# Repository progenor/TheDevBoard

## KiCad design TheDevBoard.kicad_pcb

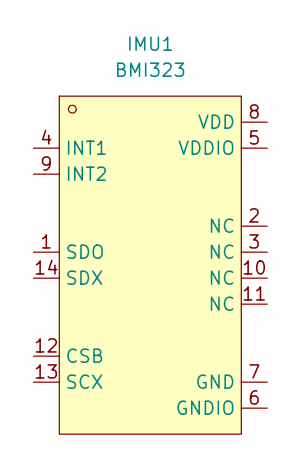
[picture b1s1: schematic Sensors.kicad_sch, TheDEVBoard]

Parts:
IMU1: BMI323; LGA-14_L3.0-W2.5-P0.50-TL_QMI8658A; MPN BMI323; LCSC Part C5368700

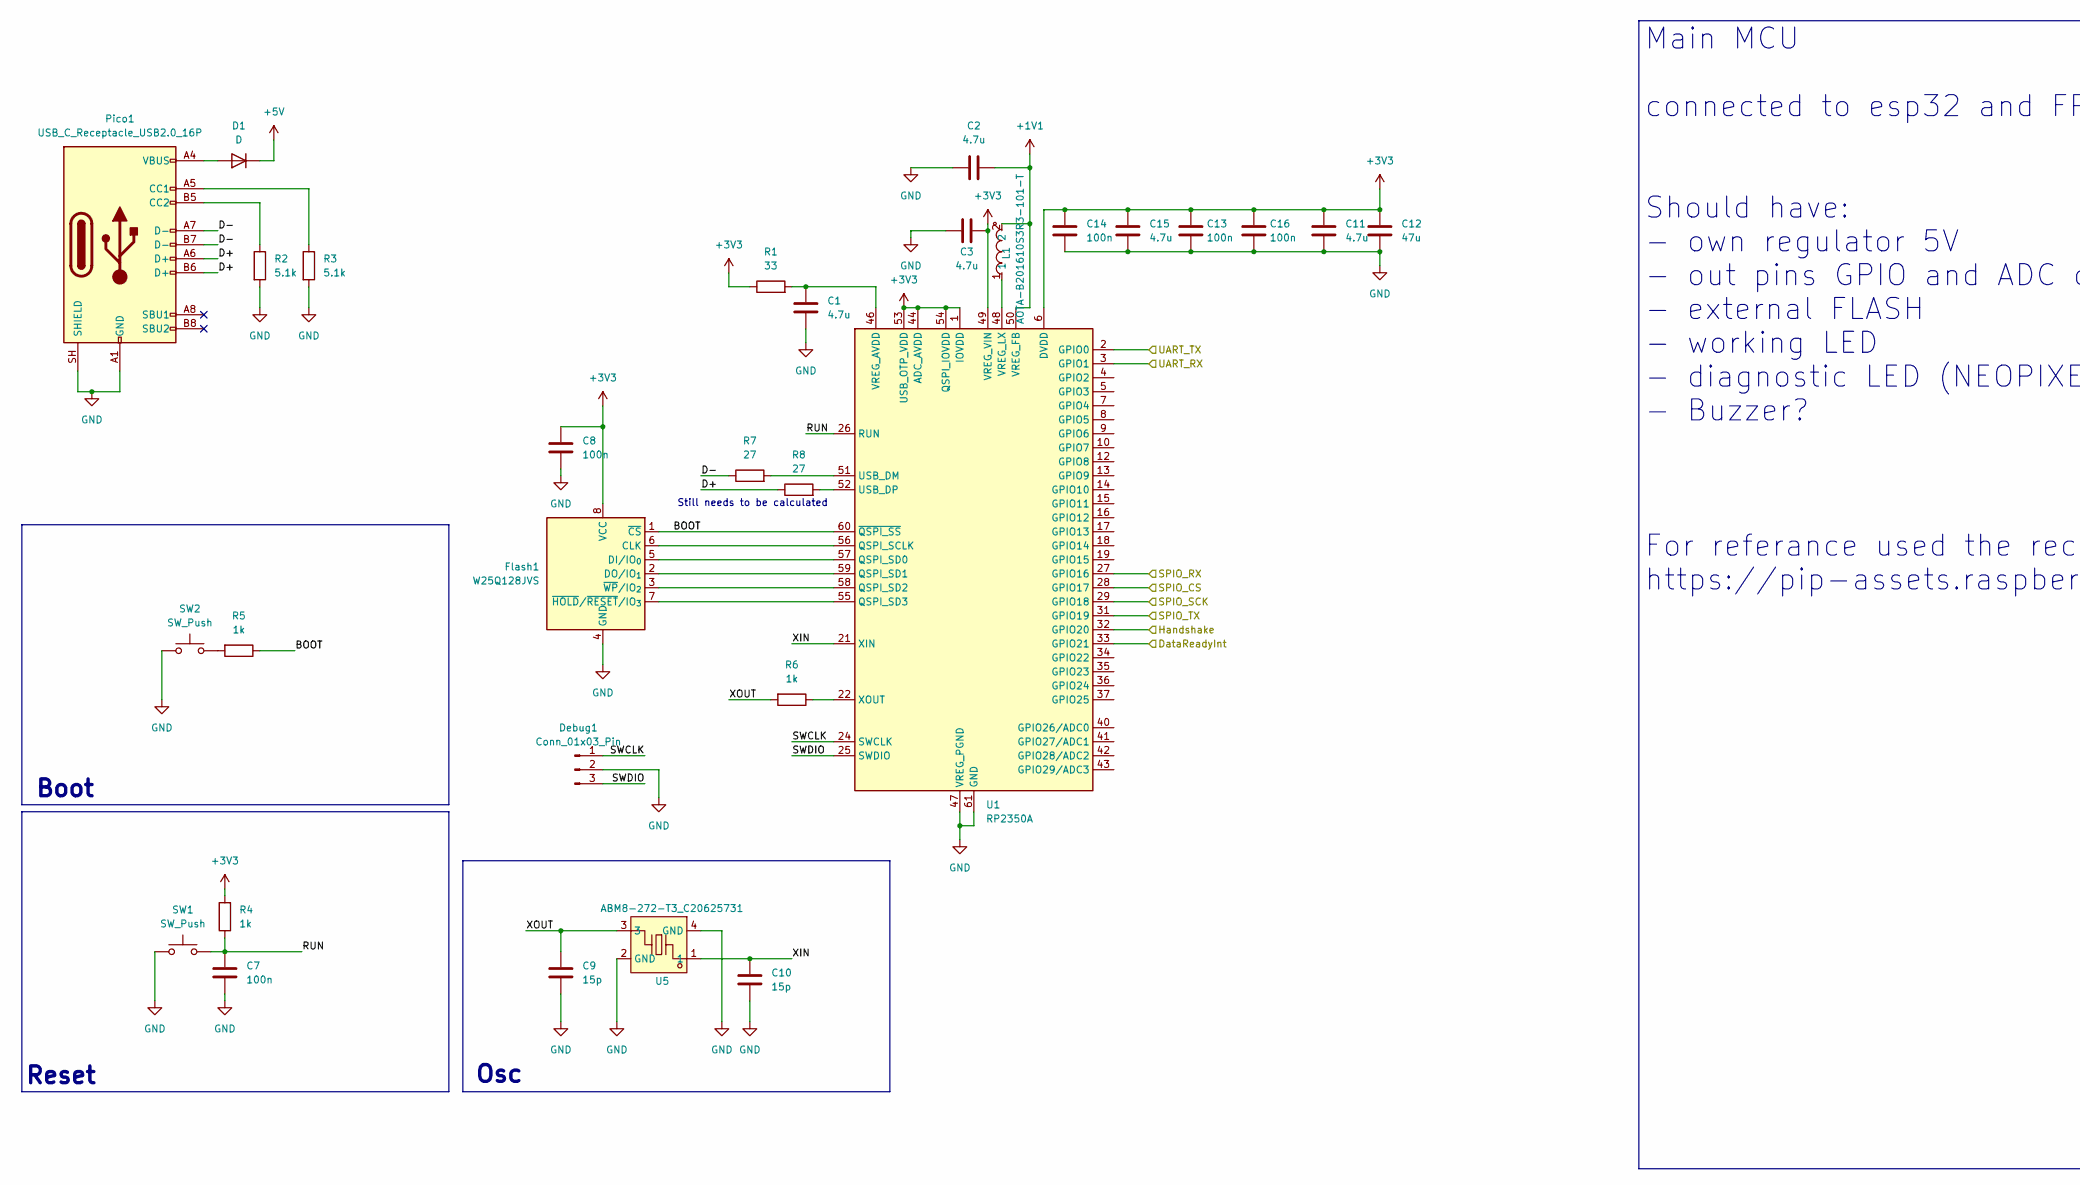
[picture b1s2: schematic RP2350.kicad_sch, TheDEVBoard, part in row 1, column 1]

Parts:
C1, C2, C3, C11, C15: 4.7u; C_0201_0603Metric_Pad0.64x0.40mm_HandSolder
C7, C8, C13, C14, C16: 100n; C_0805_2012Metric_Pad1.18x1.45mm_HandSolder
C9, C10: 15p; C_0805_2012Metric_Pad1.18x1.45mm_HandSolder
C12: 47u; C_0805_2012Metric_Pad1.18x1.45mm_HandSolder
D1: D; D_0805_2012Metric
Debug1: Conn_01x03_Pin; PinHeader_1x03_P2.54mm_Vertical
Flash1: W25Q128JVS; SOIC-8_5.3x5.3mm_P1.27mm
L1: AOTA-B201610S3R3-101-T; IND-SMD_L2.0-W1.6_AOTA-B201610S3R3-101-T; MPN AOTA-B201610S3R3-101-T; LCSC Part C42411119
Pico1: USB_C_Receptacle_USB2.0_16P; USB_C_Receptacle_XKB_U262-16XN-4BVC11
R1: 33; R_0201_0603Metric_Pad0.64x0.40mm_HandSolder
R2, R3: 5.1k; R_0805_2012Metric_Pad1.20x1.40mm_HandSolder
R4, R5, R6: 1k; R_0805_2012Metric_Pad1.20x1.40mm_HandSolder
R7, R8: 27; R_0805_2012Metric_Pad1.20x1.40mm_HandSolder
SW1, SW2: SW_Push; SW_SPST_EVQPE1
U1: RP2350A; QFN-60-1EP_7x7mm_P0.4mm_EP3.4x3.4mm
U5: ABM8-272-T3_C20625731; CRYSTAL-SMD_4P-L3.2-W2.5-BL; MPN ABM8-272-T3; LCSC Part C20625731

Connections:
+1V1: C2.2, L1.2, U1.50 (VREG_FB)
+3V3: C3.2, C8.1, C11.1, C12.1, C13.1, C14.1, C15.1, C16.1, Flash1.8 (VCC), R1.1, R4.2, U1.1 (IOVDD), U1.6 (DVDD), U1.11 (IOVDD), U1.20 (IOVDD), U1.23 (DVDD), U1.30 (IOVDD), U1.38 (IOVDD), U1.39 (DVDD), U1.44 (ADC_AVDD), U1.45 (IOVDD), U1.49 (VREG_VIN), U1.53 (USB_OTP_VDD), U1.54 (QSPI_IOVDD); also elsewhere on the board
+5V: D1.1 (K); also elsewhere on the board
/ESP32-S3-Mini-WIFI/DataReadyInt: U1.33 (GPIO21); also elsewhere on the board
/ESP32-S3-Mini-WIFI/FSPICLK: U1.29 (GPIO18); also elsewhere on the board
/ESP32-S3-Mini-WIFI/FSPICS0: U1.28 (GPIO17); also elsewhere on the board
/ESP32-S3-Mini-WIFI/FSPID: U1.31 (GPIO19); also elsewhere on the board
/ESP32-S3-Mini-WIFI/FSPIQ: U1.27 (GPIO16); also elsewhere on the board
/ESP32-S3-Mini-WIFI/Handshake: U1.32 (GPIO20); also elsewhere on the board
/ESP32-S3-Mini-WIFI/UART_RX_ESP: U1.2 (GPIO0); also elsewhere on the board
/ESP32-S3-Mini-WIFI/UART_TX_ESP: U1.3 (GPIO1); also elsewhere on the board
/RP2350/<NO NET>: Pico1.A7 (D-), Pico1.B7 (D-), R7.1
/RP2350/BOOT: Flash1.1 (~CS), R5.1, U1.60 (~QSPI_SS); also elsewhere on the board
/RP2350/D+: Pico1.A6 (D+), Pico1.B6 (D+), R8.1
/RP2350/RUN: C7.1, R4.1, SW1.2, U1.26 (RUN)
/RP2350/SWCLK: Debug1.1, U1.24 (SWCLK)
/RP2350/SWDIO: Debug1.3, U1.25 (SWDIO)
/RP2350/XIN: C10.1, U1.21 (XIN), U5.1
/RP2350/XOUT: C9.1, R6.2, U5.3
GND: C1.2, C2.1, C3.1, C7.2, C8.2, C9.2, C10.2, C11.2, C12.2, C13.2, C14.2, C15.2, C16.2, Debug1.2, Flash1.4 (GND), Pico1.A1 (GND), Pico1.A12 (GND), Pico1.B1 (GND), Pico1.B12 (GND), Pico1.SH (SHIELD), R2.2, R3.2, SW1.1, SW2.1, U1.47 (VREG_PGND), U1.61 (GND), U5.2 (GND), U5.4 (GND); also elsewhere on the board
unnamed: D1.2 (A), Pico1.A4 (VBUS), Pico1.A9 (VBUS), Pico1.B4 (VBUS), Pico1.B9 (VBUS)
unnamed: Flash1.6 (CLK), U1.56 (QSPI_SCLK)
unnamed: Flash1.5 (DI/IO_{0}), U1.57 (QSPI_SD0)
unnamed: Flash1.2 (DO/IO_{1}), U1.59 (QSPI_SD1)
unnamed: Flash1.7 (~HOLD/~RESET/IO_{3}), U1.55 (QSPI_SD3)
unnamed: Flash1.3 (~WP/IO_{2}), U1.58 (QSPI_SD2)
unnamed: Pico1.A5 (CC1), R3.1
unnamed: Pico1.B5 (CC2), R2.1
unnamed: R5.2, SW2.2
unnamed: R7.2, U1.51 (USB_DM)
unnamed: R8.2, U1.52 (USB_DP)
unnamed: C1.1, R1.2, U1.46 (VREG_AVDD)
unnamed: L1.1, U1.48 (VREG_LX)
unnamed: R6.1, U1.22 (XOUT)

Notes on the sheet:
Boot
Reset
Still needs to be calculated
Osc
Main MCU connected to esp32 and FPGA Should have: - own regulator 5V - out pins GPIO and ADC convertor - external FLASH - working LED - diagnostic LED (NEOPIXEL) - Buzzer? For referance used the recomended design by Raspbery itself https://pip-assets.raspberrypi.com/categories/1214-rp2350/documents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

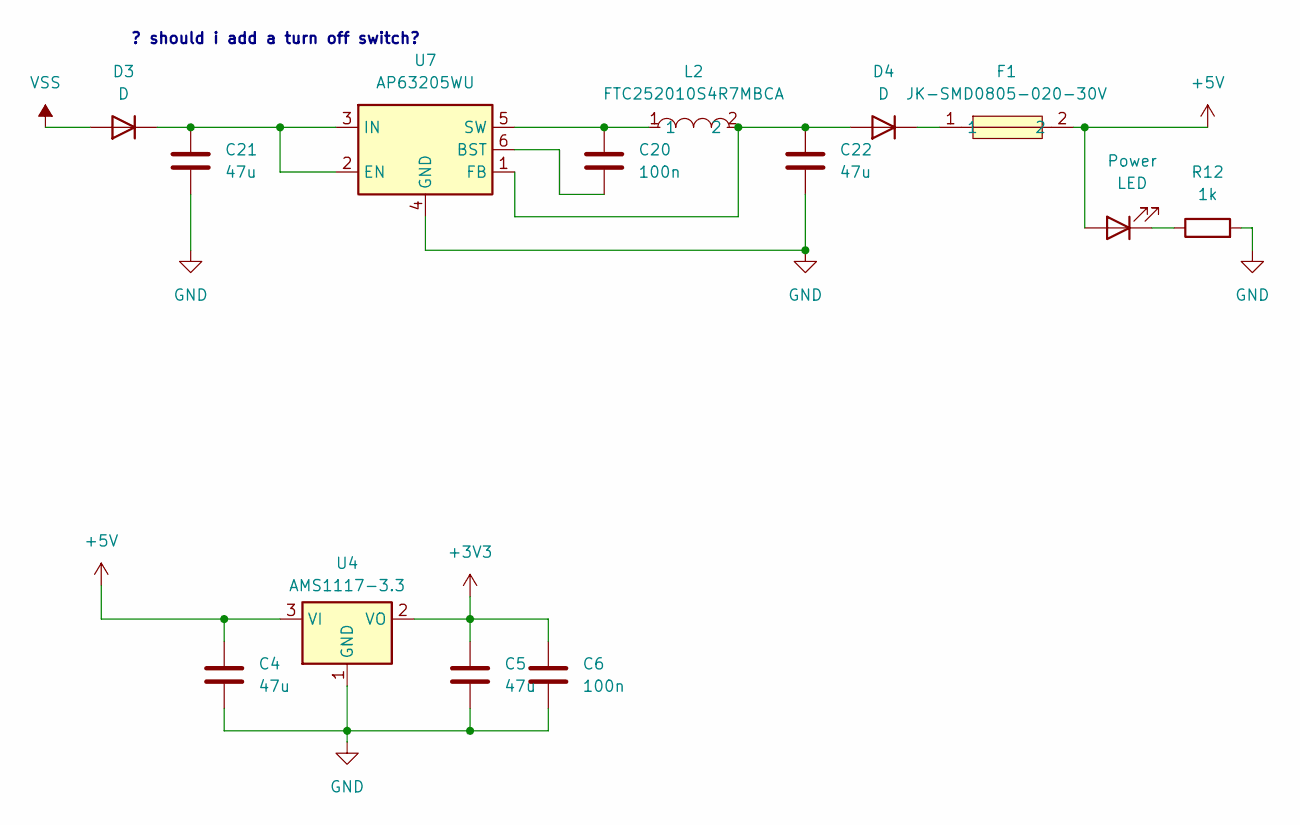
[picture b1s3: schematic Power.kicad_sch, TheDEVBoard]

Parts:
C4, C5, C21, C22: 47u; C_0805_2012Metric_Pad1.18x1.45mm_HandSolder
C6, C20: 100n; C_0805_2012Metric_Pad1.18x1.45mm_HandSolder
D3, D4: D; D_0805_2012Metric
F1: JK-SMD0805-020-30V; F0805; MPN JK-SMD0805-020-30V; LCSC Part C516070
L2: FTC252010S4R7MBCA; IND-SMD_L2.5-W2.0-VLS252012CX-150M; MPN FTC252010S4R7MBCA; LCSC Part C5832360
Power: LED; LED_0805_2012Metric
R12: 1k; R_0805_2012Metric
U4: AMS1117-3.3; SOT-223-3_TabPin2
U7: AP63205WU; TSOT-23-6_HandSoldering

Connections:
+3V3: C5.1, C6.1, U4.2 (VO); also elsewhere on the board
+5V: C4.1, F1.2, Power.2 (A), U4.3 (VI); also elsewhere on the board
GND: C4.2, C5.2, C6.2, C21.2, C22.2, R12.2, U4.1 (GND), U7.4 (GND); also elsewhere on the board
unnamed: C21.1, D3.1 (K), U7.2 (EN), U7.3 (IN)
unnamed: C22.1, D4.2 (A), L2.2, U7.1 (FB)
unnamed: D4.1 (K), F1.1
unnamed 42: Power.1 (K), R12.1; also elsewhere on the board
unnamed: C20.2, U7.6 (BST)
unnamed: C20.1, L2.1, U7.5 (SW)
VSS: D3.2 (A)

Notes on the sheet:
? should i add a turn off switch?

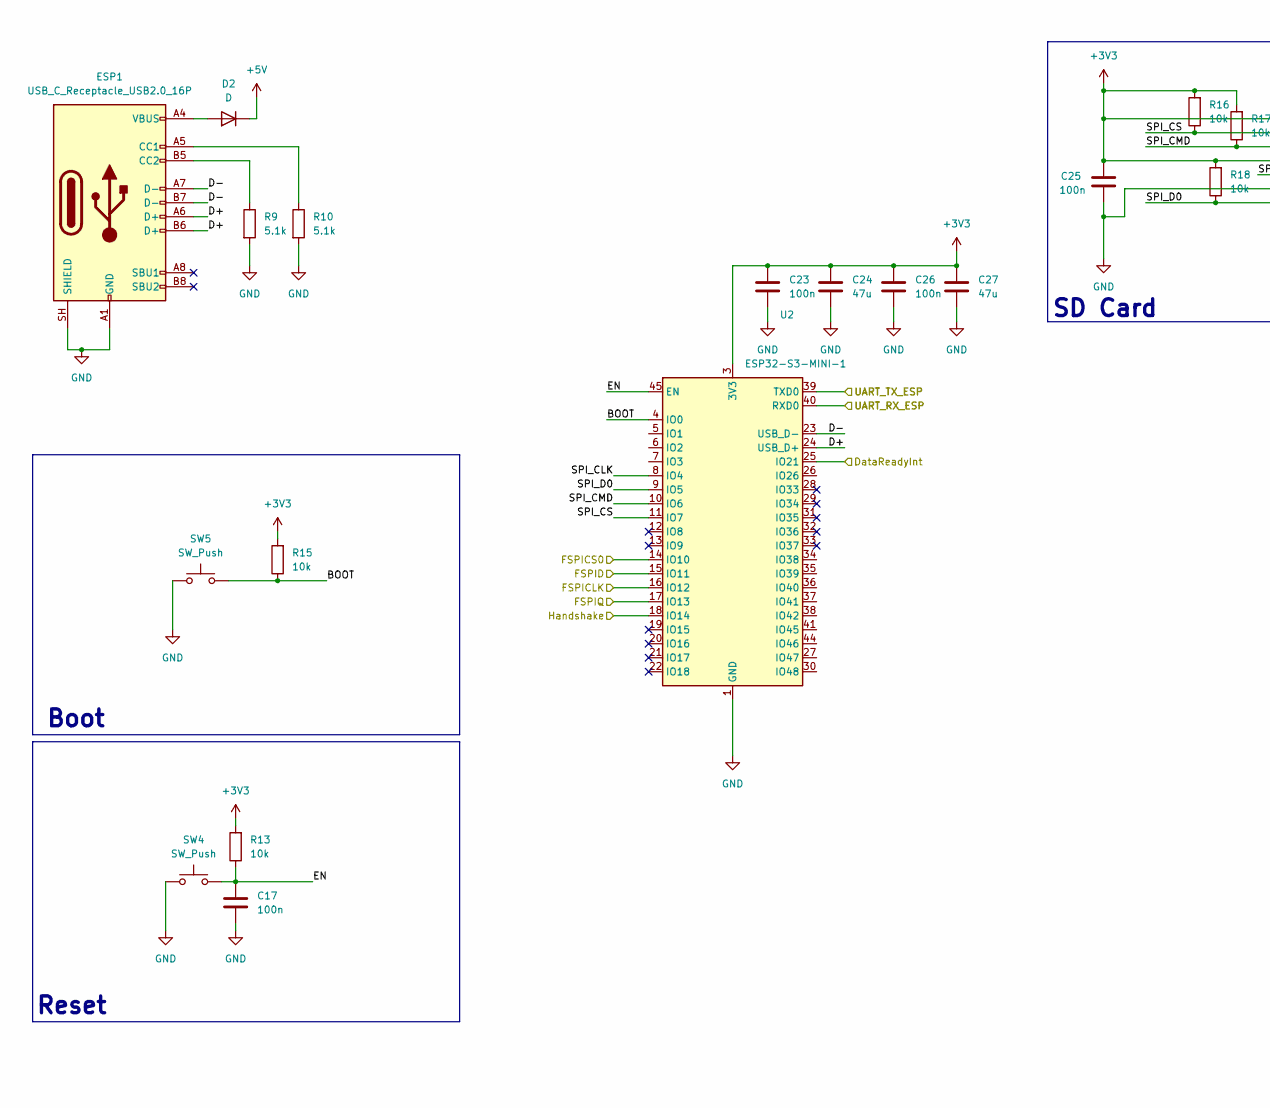
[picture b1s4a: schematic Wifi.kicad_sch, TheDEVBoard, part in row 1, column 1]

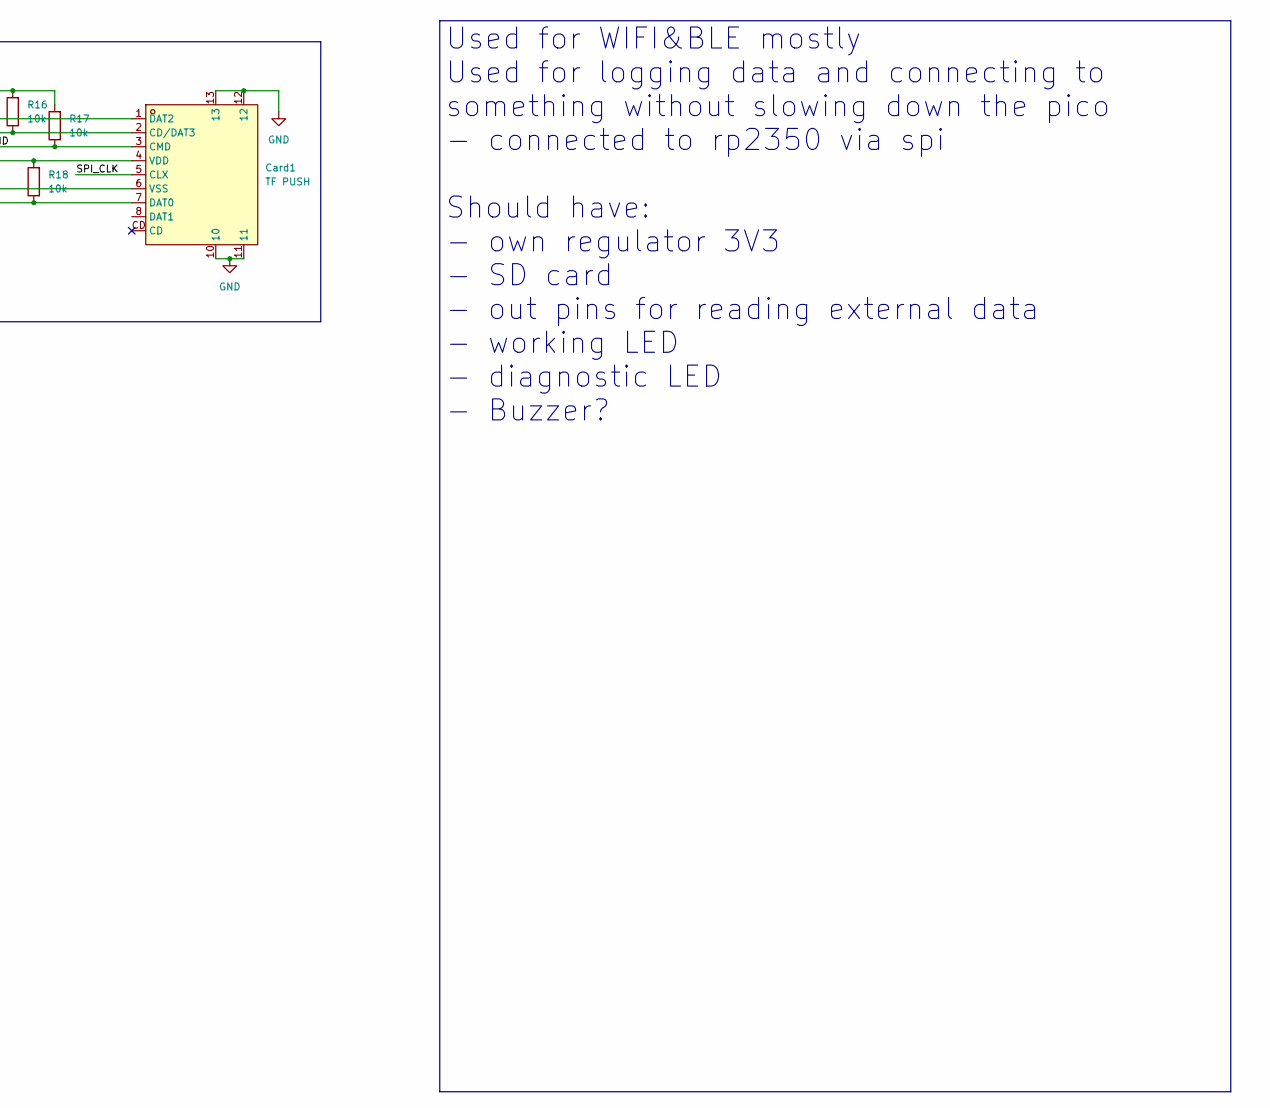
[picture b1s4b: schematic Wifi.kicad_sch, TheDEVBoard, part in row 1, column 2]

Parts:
C17, C23, C25, C26: 100n; C_0805_2012Metric_Pad1.18x1.45mm_HandSolder
C24, C27: 47u; C_0805_2012Metric_Pad1.18x1.45mm_HandSolder
Card1: TF PUSH; TF-SMD_TF-PUSH; MPN TF PUSH; LCSC Part C393941
D2: D; D_0805_2012Metric
ESP1: USB_C_Receptacle_USB2.0_16P; USB_C_Receptacle_XKB_U262-16XN-4BVC11
R9, R10: 5.1k; R_0805_2012Metric_Pad1.20x1.40mm_HandSolder
R13, R15, R16, R17, R18: 10k; R_0805_2012Metric_Pad1.20x1.40mm_HandSolder
SW4, SW5: SW_Push; SW_SPST_EVQPE1
U2: ESP32-S3-MINI-1; ESP32-S2-MINI-1

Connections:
+3V3: C23.1, C24.1, C25.1, C26.1, C27.1, Card1.1 (DAT2), Card1.4 (VDD), R13.2, R15.2, R16.2, R17.2, R18.2, U2.3 (3V3); also elsewhere on the board
+5V: D2.1 (K); also elsewhere on the board
/ESP32-S3-Mini-WIFI/BOOT: R15.1, SW5.2, U2.4 (IO0)
/ESP32-S3-Mini-WIFI/D+: ESP1.A6 (D+), ESP1.B6 (D+), U2.24 (USB_D+)
/ESP32-S3-Mini-WIFI/D-: ESP1.A7 (D-), ESP1.B7 (D-), U2.23 (USB_D-)
/ESP32-S3-Mini-WIFI/DataReadyInt: U2.25 (IO21); also elsewhere on the board
/ESP32-S3-Mini-WIFI/EN: C17.1, R13.1, SW4.2, U2.45 (EN)
/ESP32-S3-Mini-WIFI/FSPICLK: U2.16 (IO12); also elsewhere on the board
/ESP32-S3-Mini-WIFI/FSPICS0: U2.14 (IO10); also elsewhere on the board
/ESP32-S3-Mini-WIFI/FSPID: U2.15 (IO11); also elsewhere on the board
/ESP32-S3-Mini-WIFI/FSPIQ: U2.17 (IO13); also elsewhere on the board
/ESP32-S3-Mini-WIFI/Handshake: U2.18 (IO14); also elsewhere on the board
/ESP32-S3-Mini-WIFI/SPI_CLK: Card1.5 (CLX), U2.8 (IO4)
/ESP32-S3-Mini-WIFI/SPI_CMD: Card1.3 (CMD), R17.1, U2.10 (IO6)
/ESP32-S3-Mini-WIFI/SPI_CS: Card1.2 (CD/DAT3), R16.1, U2.11 (IO7)
/ESP32-S3-Mini-WIFI/SPI_D0: Card1.7 (DAT0), R18.1, U2.9 (IO5)
/ESP32-S3-Mini-WIFI/UART_RX_ESP: U2.40 (RXD0); also elsewhere on the board
/ESP32-S3-Mini-WIFI/UART_TX_ESP: U2.39 (TXD0); also elsewhere on the board
GND: C17.2, C23.2, C24.2, C25.2, C26.2, C27.2, Card1.6 (VSS), Card1.10, Card1.11, Card1.12, Card1.13, ESP1.A1 (GND), ESP1.A12 (GND), ESP1.B1 (GND), ESP1.B12 (GND), ESP1.SH (SHIELD), R9.2, R10.2, SW4.1, SW5.1, U2.1 (GND), U2.2 (GND), U2.42 (GND), U2.43 (GND), U2.46 (GND), U2.47 (GND), U2.48 (GND), U2.49 (GND), U2.50 (GND), U2.51 (GND), U2.52 (GND), U2.53 (GND), U2.54 (GND), U2.55 (GND), U2.56 (GND), U2.57 (GND), U2.58 (GND), U2.59 (GND), U2.60 (GND), U2.61 (GND), U2.62 (GND), U2.63 (GND), U2.64 (GND), U2.65 (GND); also elsewhere on the board
unnamed: D2.2 (A), ESP1.A4 (VBUS), ESP1.A9 (VBUS), ESP1.B4 (VBUS), ESP1.B9 (VBUS)
unnamed: ESP1.A5 (CC1), R10.1
unnamed: ESP1.B5 (CC2), R9.1

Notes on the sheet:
Boot
Reset
SD Card
Used for WIFI&BLE mostly Used for logging data and connecting to something without slowing down the pico - connected to rp2350 via spi Should have: - own regulator 3V3 - SD card - out pins for reading external data - working LED - diagnostic LED - Buzzer?

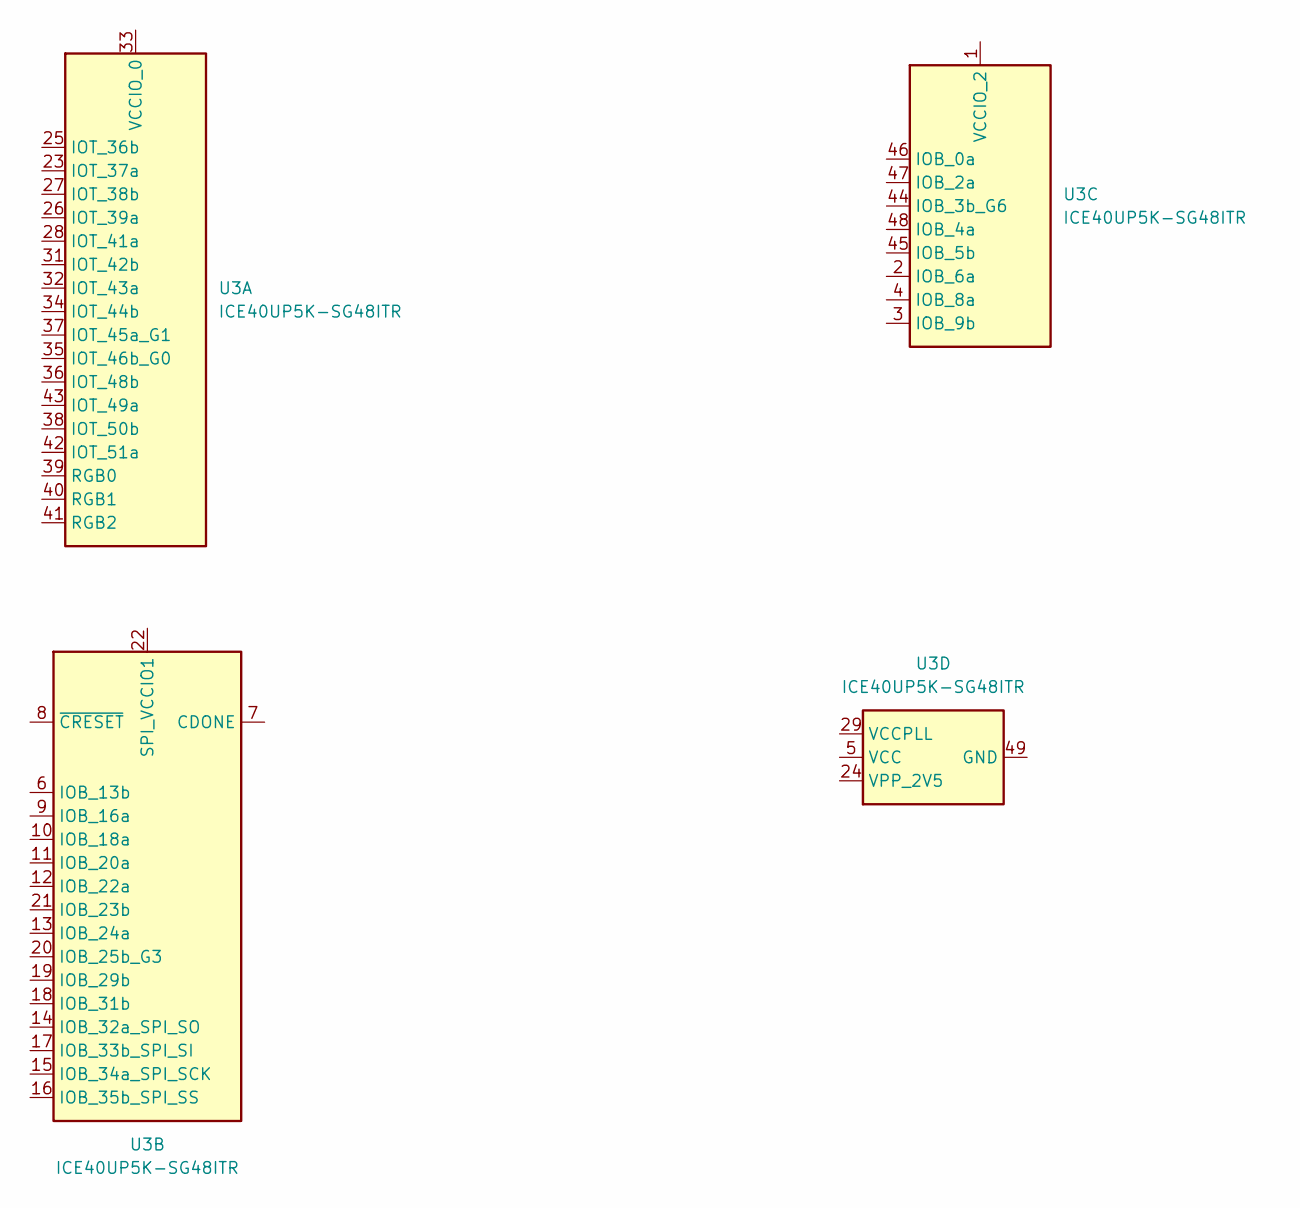
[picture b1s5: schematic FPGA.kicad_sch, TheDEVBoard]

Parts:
U3: ICE40UP5K-SG48ITR; QFN-48-1EP_7x7mm_P0.5mm_EP5.6x5.6mm_ThermalVias

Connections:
unnamed: U3.5 (VCC), U3.30 (VCC)

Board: 2 copper layers, 67 parts (0 on the bottom side), 53 nets, no tracks yet.

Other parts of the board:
Power1: LED; LED_0805_2012Metric
R11: 1k; R_0805_2012Metric_Pad1.20x1.40mm_HandSolder
SW3: SW_Push; SW_SPST_EVQPE1

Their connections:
+5V: Power1.2 (A); also elsewhere on the board
/RP2350/BOOT: R11.1; also elsewhere on the board
GND: SW3.1; also elsewhere on the board
unnamed 42: Power1.1 (K); also elsewhere on the board
unnamed: R11.2, SW3.2

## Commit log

2026-06-04 init
2026-06-04 worked on some shit
2026-06-04 added some lcsc part numbers
2026-06-04 created esp32 s3 mini connection to rp2350 added SD card Routed them together
2026-06-04 generated pdf
